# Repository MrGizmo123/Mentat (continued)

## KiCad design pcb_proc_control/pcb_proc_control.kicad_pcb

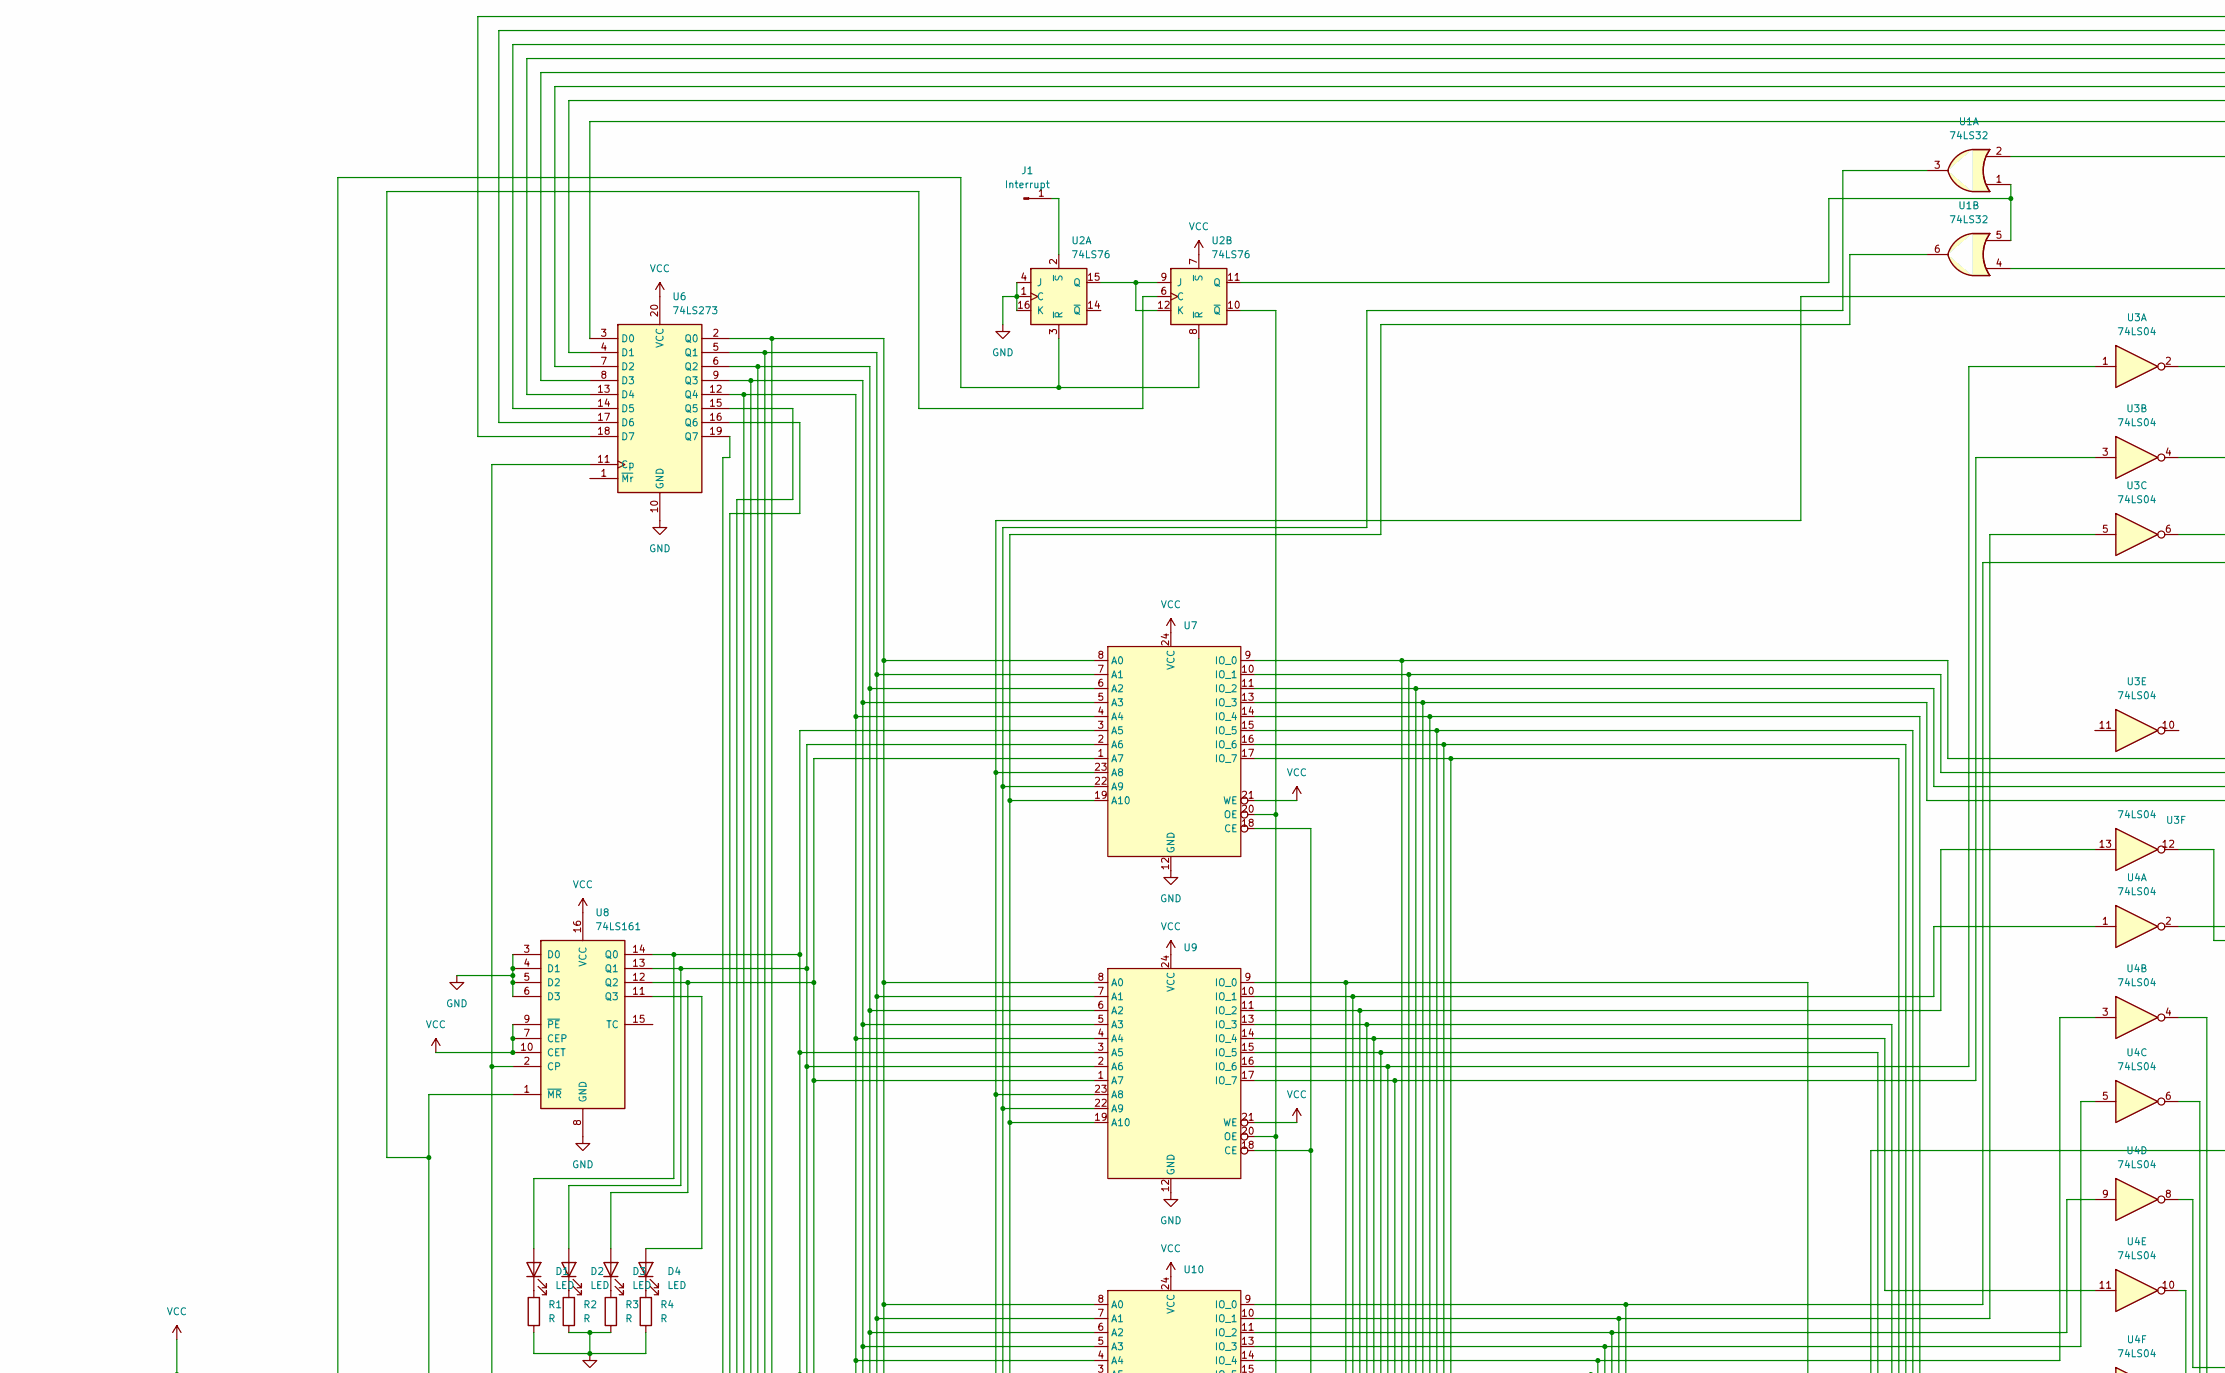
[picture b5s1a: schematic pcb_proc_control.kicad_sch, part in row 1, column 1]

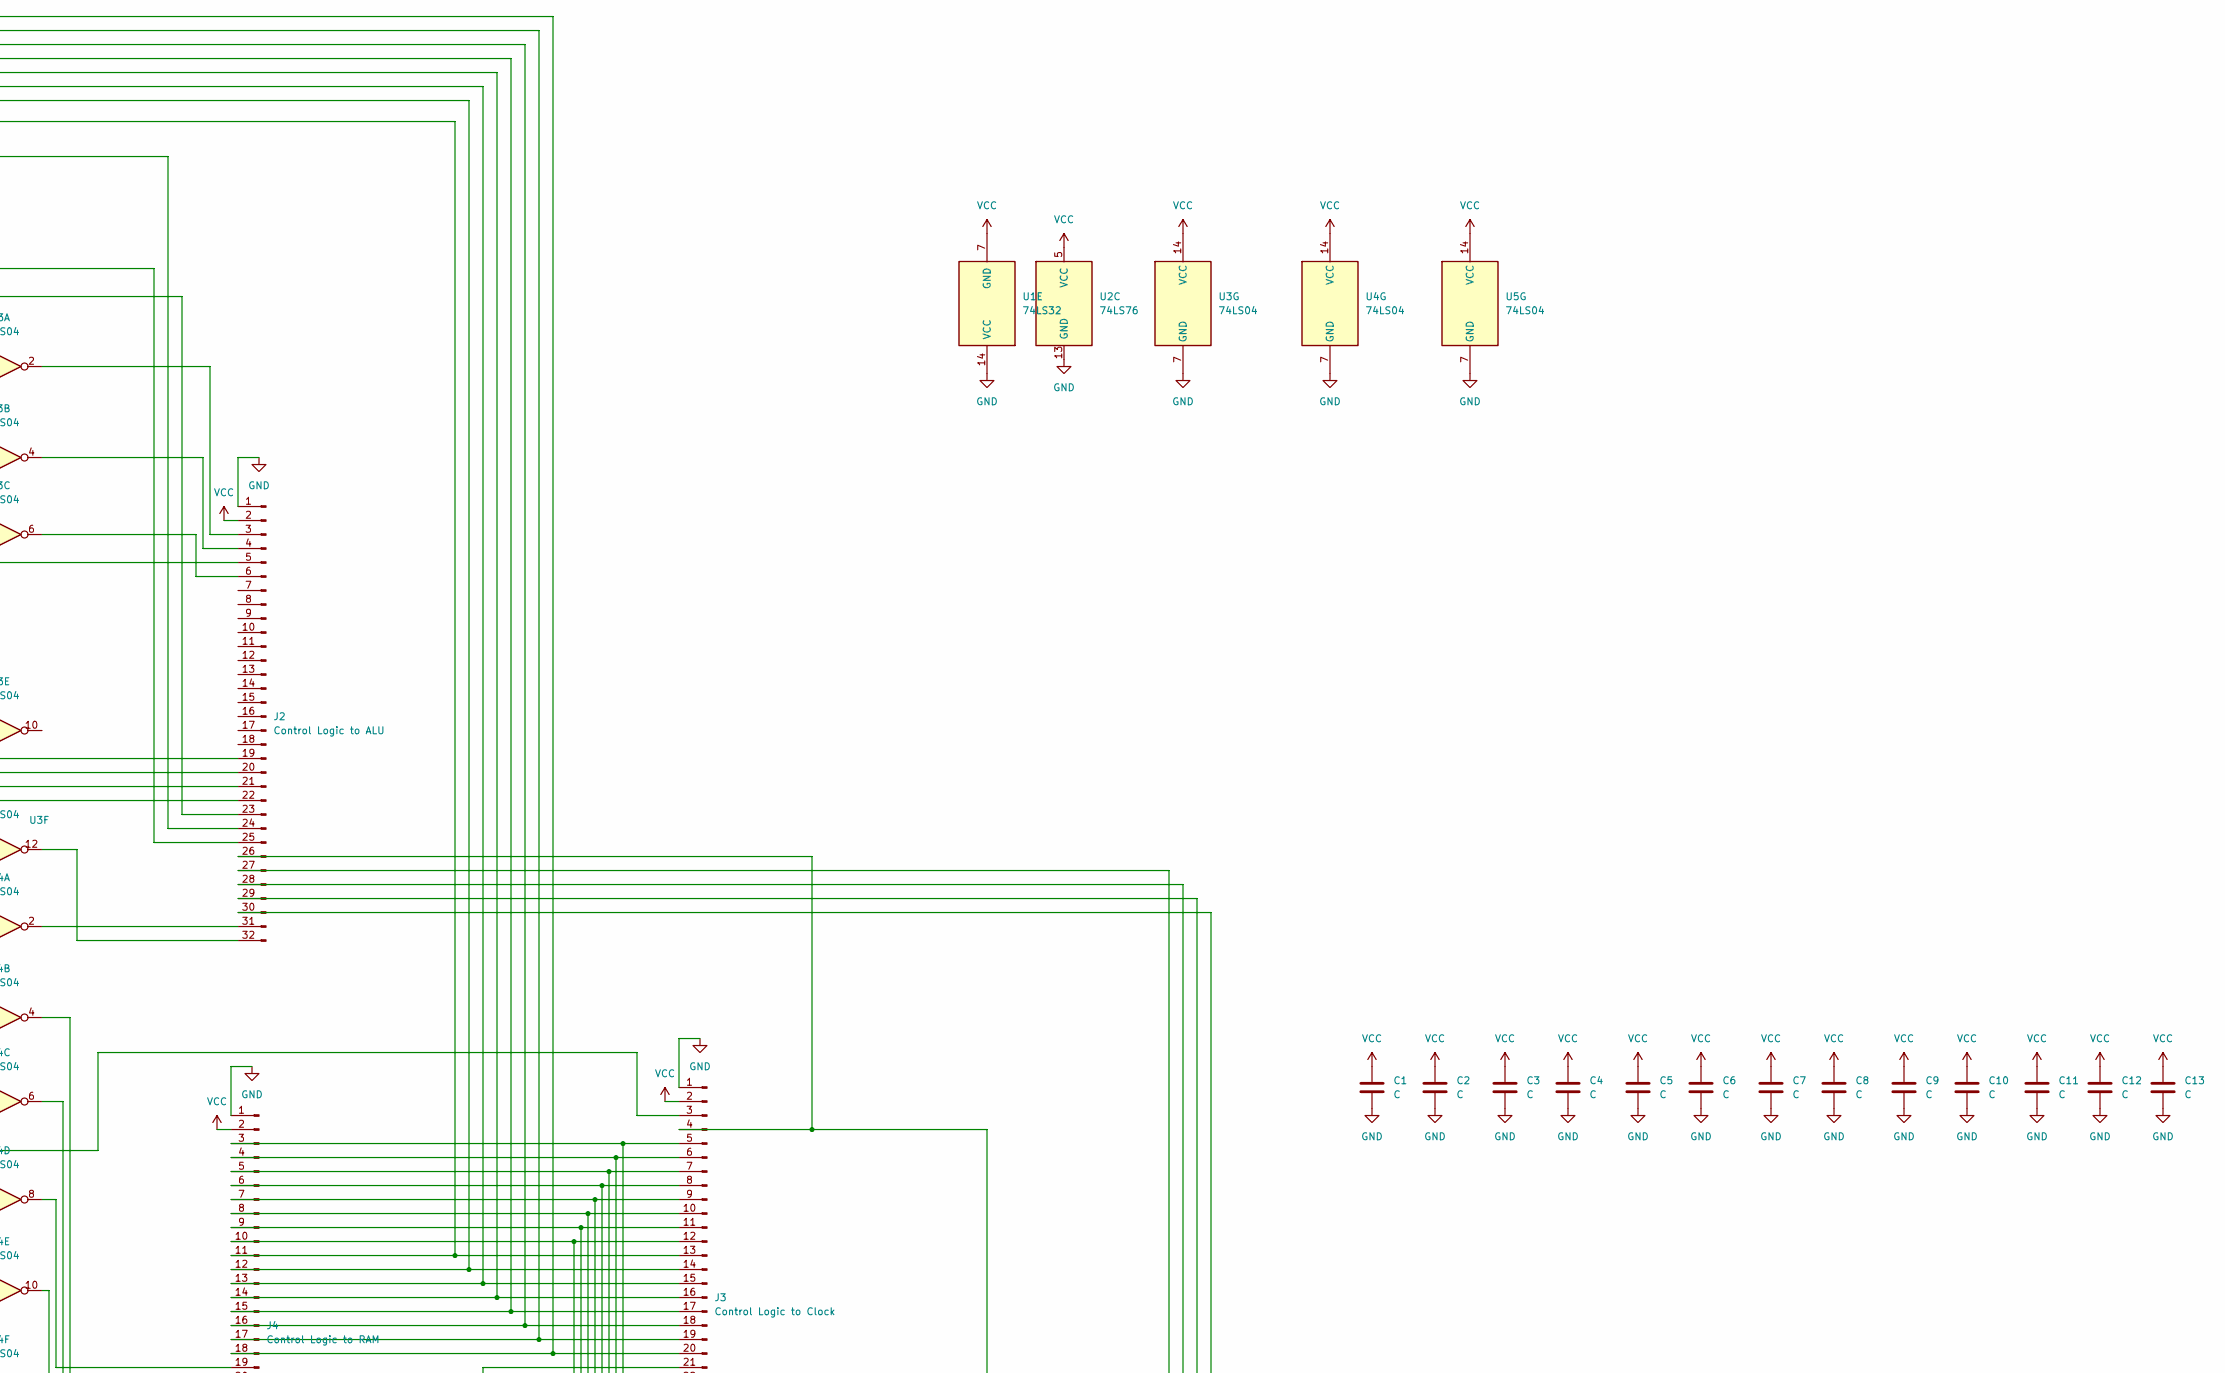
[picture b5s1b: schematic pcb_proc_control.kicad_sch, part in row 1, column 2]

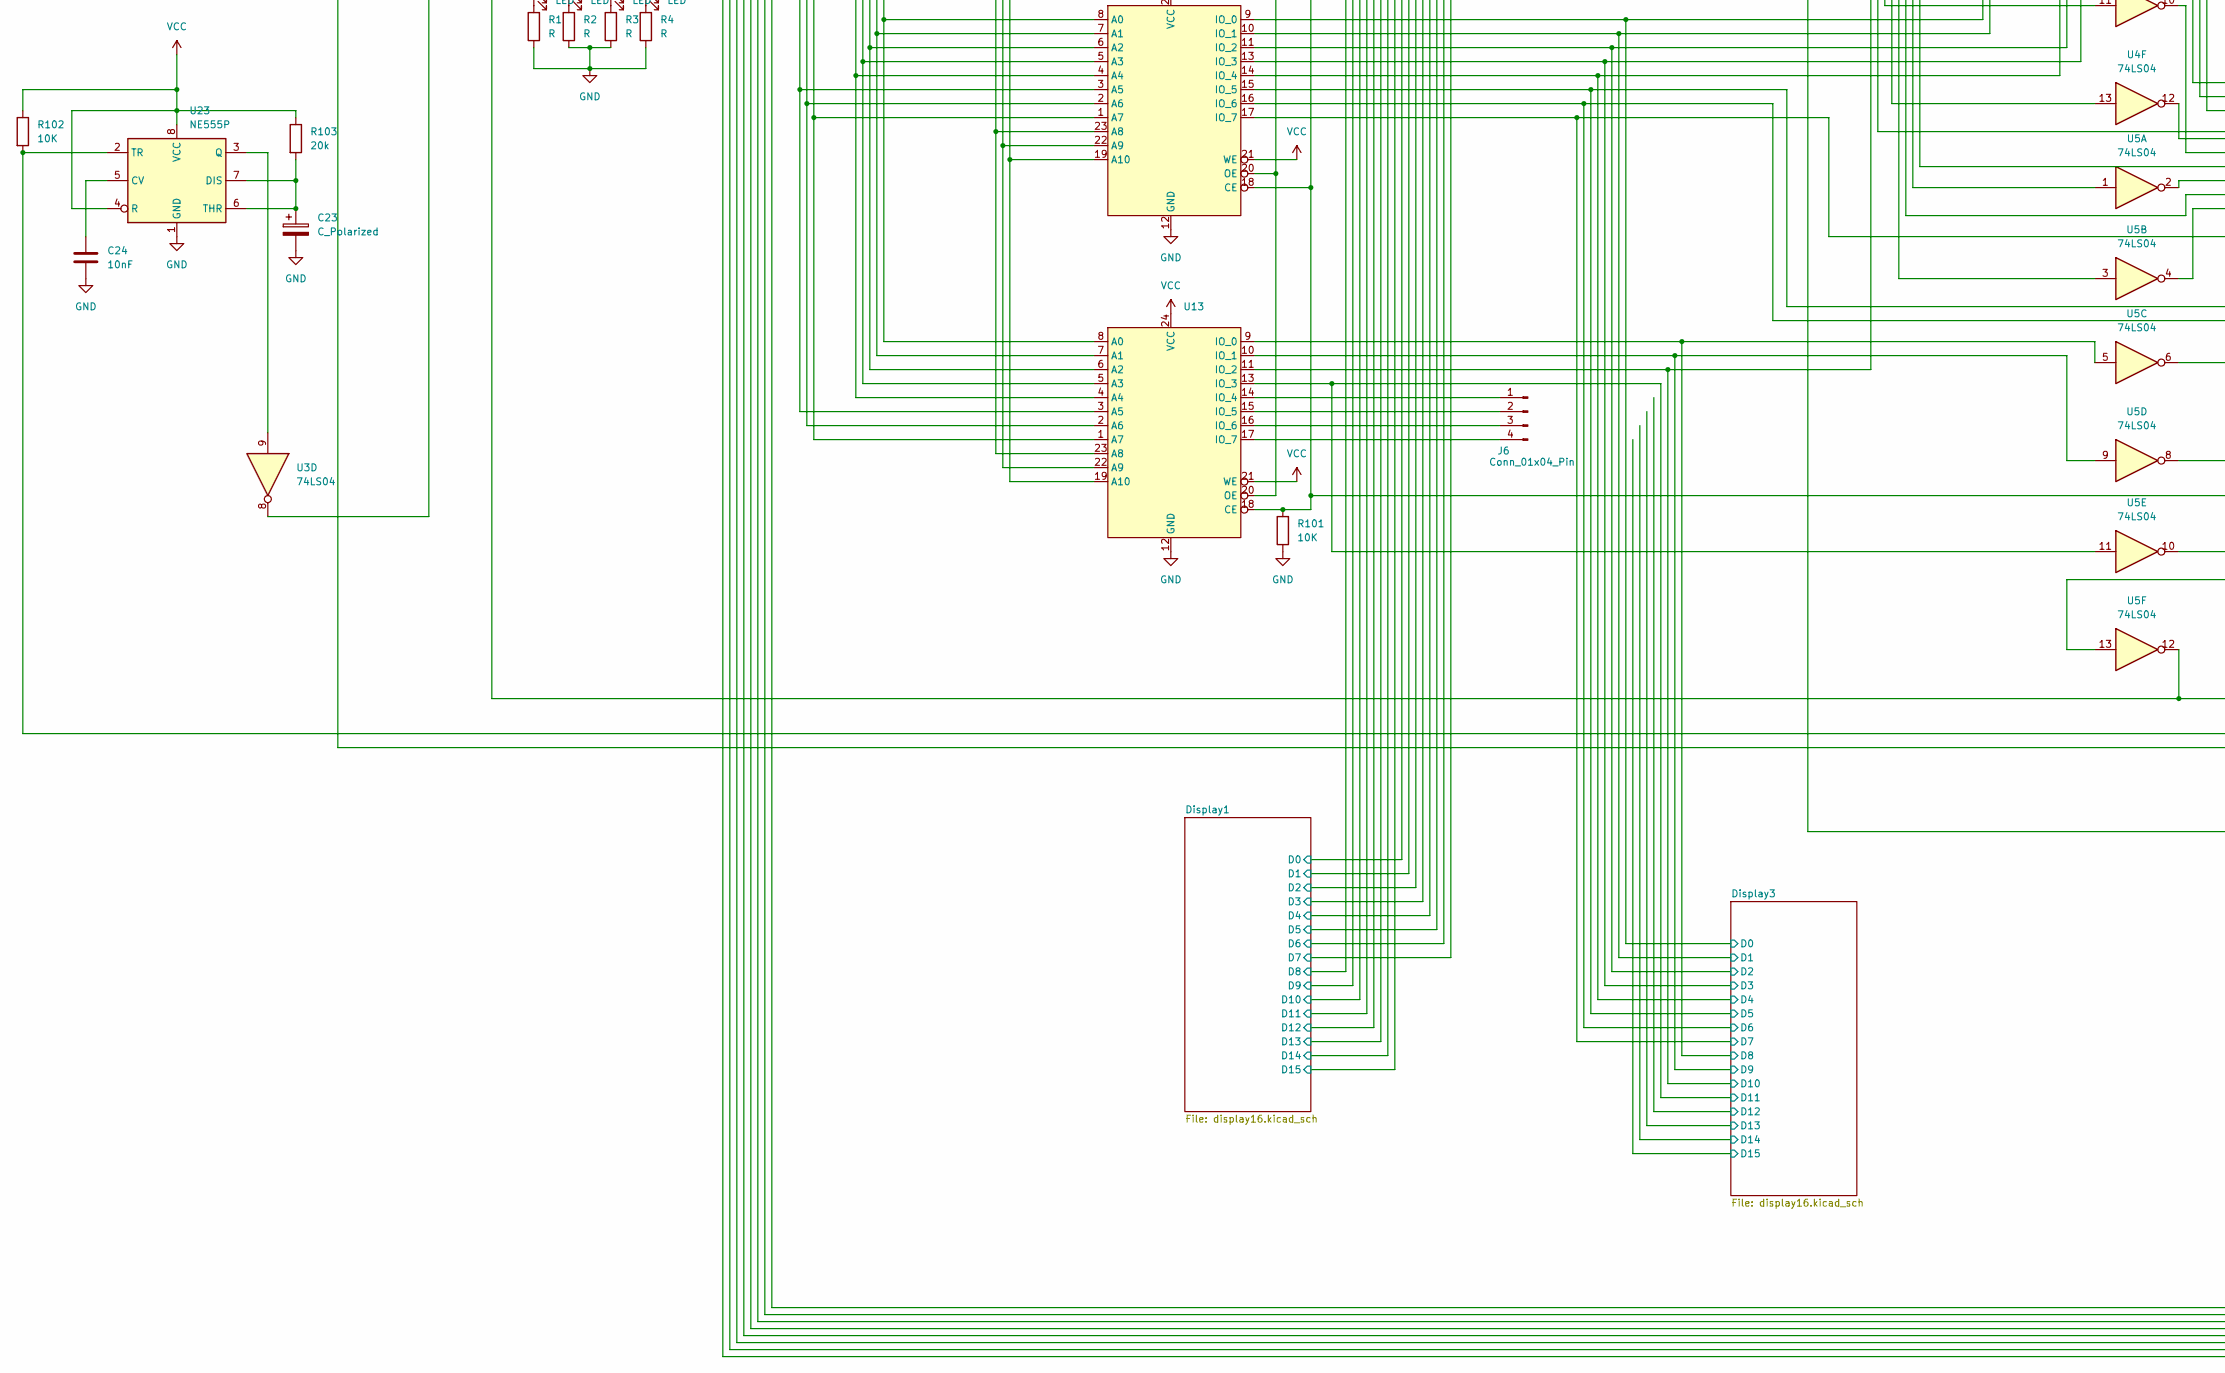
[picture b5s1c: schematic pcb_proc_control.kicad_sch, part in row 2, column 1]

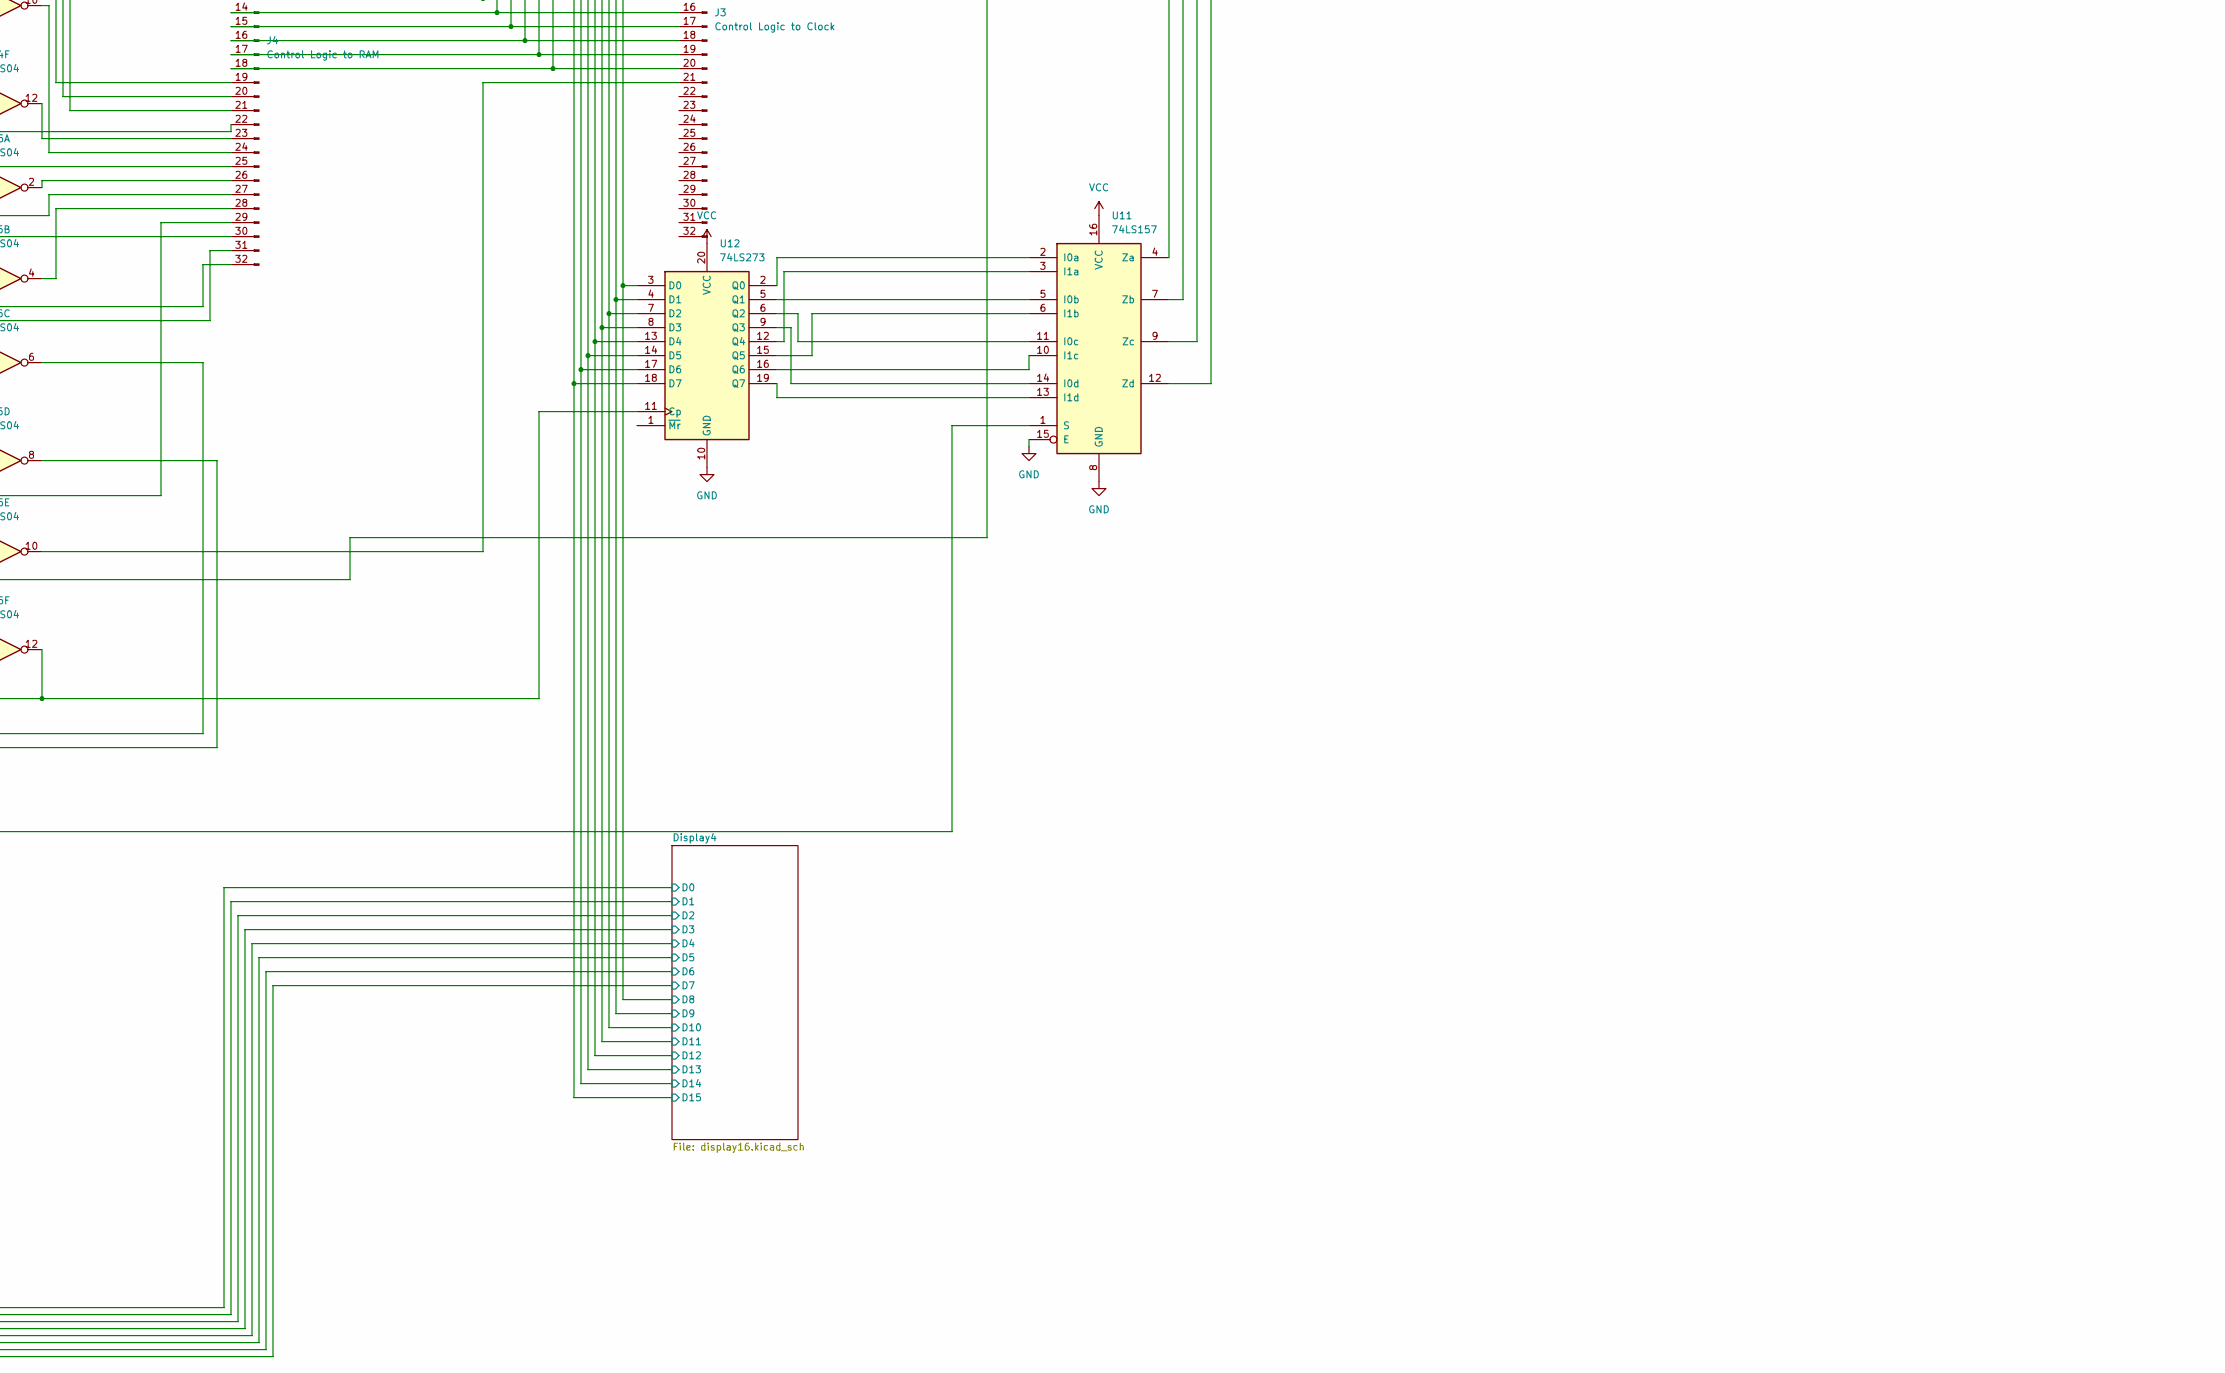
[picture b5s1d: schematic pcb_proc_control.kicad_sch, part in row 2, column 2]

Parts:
C1, C2, C3, C4, C5, C6, C7, C8, C9, C10, C11, C12, C13: C; C_0805_2012Metric
C23: C_Polarized; CP_Radial_D4.0mm_P1.50mm
C24: 10nF; C_Disc_D3.0mm_W1.6mm_P2.50mm
D1, D2, D3, D4: LED; LED_Rectangular_W5.0mm_H2.0mm
J1: Interrupt; PinHeader_1x01_P2.54mm_Vertical
J2: Control Logic to ALU; PinHeader_2x16_P2.54mm_Vertical
J3: Control Logic to Clock; PinHeader_2x16_P2.54mm_Vertical
J4: Control Logic to RAM; PinHeader_2x16_P2.54mm_Vertical
J6: Conn_01x04_Pin; PinHeader_1x04_P2.54mm_Vertical
R1, R2, R3, R4: R; R_0805_2012Metric
R101, R102: 10K; R_0805_2012Metric
R103: 20k; R_0805_2012Metric
U1: 74LS32; DIP-14_W7.62mm_Socket_LongPads
U2: 74LS76; DIP-16_W7.62mm_Socket_LongPads
U3, U4, U5: 74LS04; DIP-14_W7.62mm_Socket_LongPads
U6, U12: 74LS273; DIP-20_W7.62mm_Socket_LongPads
U7, U9, U10, U13: DIP-24_W15.24mm_Socket_LongPads
U8: 74LS161; DIP-16_W7.62mm_Socket_LongPads
U11: 74LS157; DIP-16_W7.62mm_Socket_LongPads
U23: NE555P; DIP-8_W7.62mm_Socket_LongPads

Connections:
/Display1/D0: J2.19, U7.9 (IO_0); also elsewhere on the board
/Display1/D1: J2.20, U7.10 (IO_1); also elsewhere on the board
/Display1/D2: J2.21, U7.11 (IO_2); also elsewhere on the board
/Display1/D3: J2.22, U7.13 (IO_3); also elsewhere on the board
/Display1/D4: J4.25, U7.14 (IO_4); also elsewhere on the board
/Display1/D5: U5.1, U7.15 (IO_5); also elsewhere on the board
/Display1/D6: J4.27, U7.16 (IO_6); also elsewhere on the board
/Display1/D7: U5.3, U7.17 (IO_7); also elsewhere on the board
/Display1/D8: U9.9 (IO_0), U11.1 (S); also elsewhere on the board
/Display1/D9: U4.1, U9.10 (IO_1); also elsewhere on the board
/Display1/D10: U3.13, U9.11 (IO_2); also elsewhere on the board
/Display1/D11: U4.13, U9.13 (IO_3); also elsewhere on the board
/Display1/D12: U4.11, U9.14 (IO_4); also elsewhere on the board
/Display1/D13: J4.22, U9.15 (IO_5); also elsewhere on the board
/Display1/D14: U3.1, U9.16 (IO_6); also elsewhere on the board
/Display1/D15: U3.3, U9.17 (IO_7); also elsewhere on the board
/Display3/D0: J2.5, U10.9 (IO_0); also elsewhere on the board
/Display3/D1: U3.5, U10.10 (IO_1); also elsewhere on the board
/Display3/D2: U4.9, U10.11 (IO_2); also elsewhere on the board
/Display3/D3: U4.5, U10.13 (IO_3); also elsewhere on the board
/Display3/D4: U4.3, U10.14 (IO_4); also elsewhere on the board
/Display3/D5: J4.32, U10.15 (IO_5); also elsewhere on the board
/Display3/D6: J4.31, U10.16 (IO_6); also elsewhere on the board
/Display3/D7: J4.30, U10.17 (IO_7); also elsewhere on the board
/Display3/D8: U5.5, U13.9 (IO_0); also elsewhere on the board
/Display3/D9: U5.9, U13.10 (IO_1); also elsewhere on the board
/Display3/D10: J3.3, U13.11 (IO_2); also elsewhere on the board
/Display3/D11: U5.11, U13.13 (IO_3); also elsewhere on the board
/Display4/D0: U6.2 (Q0), U7.8 (A0), U9.8 (A0), U10.8 (A0), U13.8 (A0); also elsewhere on the board
/Display4/D1: U6.5 (Q1), U7.7 (A1), U9.7 (A1), U10.7 (A1), U13.7 (A1); also elsewhere on the board
/Display4/D2: U6.6 (Q2), U7.6 (A2), U9.6 (A2), U10.6 (A2), U13.6 (A2); also elsewhere on the board
/Display4/D3: U6.9 (Q3), U7.5 (A3), U9.5 (A3), U10.5 (A3), U13.5 (A3); also elsewhere on the board
/Display4/D4: U6.12 (Q4), U7.4 (A4), U9.4 (A4), U10.4 (A4), U13.4 (A4); also elsewhere on the board
/Display4/D5: U6.15 (Q5); also elsewhere on the board
/Display4/D6: U6.16 (Q6); also elsewhere on the board
/Display4/D7: U6.19 (Q7); also elsewhere on the board
/Display4/D8: J3.5, J4.3, U12.3 (D0); also elsewhere on the board
/Display4/D9: J3.6, J4.4, U12.4 (D1); also elsewhere on the board
/Display4/D10: J3.7, J4.5, U12.7 (D2); also elsewhere on the board
/Display4/D11: J3.8, J4.6, U12.8 (D3); also elsewhere on the board
/Display4/D12: J3.9, J4.7, U12.13 (D4); also elsewhere on the board
/Display4/D13: J3.10, J4.8, U12.14 (D5); also elsewhere on the board
/Display4/D14: J3.11, J4.9, U12.17 (D6); also elsewhere on the board
/Display4/D15: J3.12, J4.10, U12.18 (D7); also elsewhere on the board
GND: C1.2, C2.2, C3.2, C4.2, C5.2, C6.2, C7.2, C8.2, C9.2, C10.2, C11.2, C12.2, C13.2, C23.2, C24.2, J2.1, J3.1, J4.1, R1.1, R2.1, R3.1, R4.1, R101.1, U1.14 (VCC), U2.1 (C), U2.4 (J), U2.13 (GND), U2.16 (K), U3.7 (GND), U4.7 (GND), U5.7 (GND), U6.10 (GND), U7.12 (GND), U8.3 (D0), U8.4 (D1), U8.5 (D2), U8.6 (D3), U8.8 (GND), U9.12 (GND), U10.12 (GND), U11.8 (GND), U11.15 (E), U12.10 (GND), U13.12 (GND), U23.1 (GND); also elsewhere on the board
unnamed: D1.2 (A), U7.3 (A5), U8.14 (Q0), U9.3 (A5), U10.3 (A5), U13.3 (A5)
unnamed: D1.1 (K), R1.2
unnamed: D2.2 (A), U7.2 (A6), U8.13 (Q1), U9.2 (A6), U10.2 (A6), U13.2 (A6)
unnamed: D2.1 (K), R2.2
unnamed: D3.2 (A), U7.1 (A7), U8.12 (Q2), U9.1 (A7), U10.1 (A7), U13.1 (A7)
unnamed: D3.1 (K), R3.2
unnamed: D4.2 (A), U8.11 (Q3)
unnamed: D4.1 (K), R4.2
unnamed: J1.1, U2.2 (~S)
unnamed: J2.3, U3.2
unnamed: J2.4, U3.4
unnamed: J2.6, U3.6
unnamed: J2.23, U7.23 (A8), U9.23 (A8), U10.23 (A8), U13.23 (A8)
unnamed: J2.24, U1.2
unnamed: J2.25, U1.4
unnamed: J2.26, J3.4, U5.13
unnamed: J2.27, U11.4 (Za)
unnamed: J2.28, U11.7 (Zb)
unnamed: J2.29, U11.9 (Zc)
unnamed: J2.30, U11.12 (Zd)
unnamed: J2.31, U4.2
unnamed: J2.32, U3.12
unnamed: J3.13, J4.11, U6.3 (D0)
unnamed: J3.14, J4.12, U6.4 (D1)
unnamed: J3.15, J4.13, U6.7 (D2)
unnamed: J3.16, J4.14, U6.8 (D3)
unnamed: J3.17, J4.15, U6.13 (D4)
unnamed: J3.18, J4.16, U6.14 (D5)
unnamed: J3.19, J4.17, U6.17 (D6)
unnamed: J3.20, J4.18, U6.18 (D7)
unnamed: J3.21, U5.10
unnamed: J4.19, U4.8
unnamed: J4.20, U4.6
unnamed: J4.21, U4.4
unnamed: J4.23, U4.12
unnamed: J4.24, U4.10
unnamed: J4.26, U5.2
unnamed: J4.28, U5.4
unnamed: J4.29, R101.2, U7.18 (CE), U9.18 (CE), U10.18 (CE), U13.18 (CE)
unnamed: J6.1, U13.14 (IO_4)
unnamed: J6.2, U13.15 (IO_5)
unnamed: J6.3, U13.16 (IO_6)
unnamed: J6.4, U13.17 (IO_7)
unnamed: U2.9 (J), U2.12 (K), U2.15 (Q)
unnamed: U2.3 (~R), U2.8 (~R), U5.8
unnamed: U2.6 (C), U3.8, U8.1 (~MR)
unnamed: U1.1, U1.5, U2.11 (Q)
unnamed: U1.3, U7.22 (A9), U9.22 (A9), U10.22 (A9), U13.22 (A9)
unnamed: U1.6, U7.19 (A10), U9.19 (A10), U10.19 (A10), U13.19 (A10)
unnamed: U2.10 (~Q), U7.20 (OE), U9.20 (OE), U10.20 (OE), U13.20 (OE)
unnamed: U11.2 (I0a), U12.2 (Q0)
unnamed: U11.5 (I0b), U12.5 (Q1)
unnamed: U11.11 (I0c), U12.6 (Q2)
unnamed: U11.14 (I0d), U12.9 (Q3)
unnamed: U11.3 (I1a), U12.12 (Q4)
unnamed: U11.6 (I1b), U12.15 (Q5)
unnamed: U11.10 (I1c), U12.16 (Q6)
unnamed: U11.13 (I1d), U12.19 (Q7)
unnamed: U5.12, U6.11 (Cp), U8.2 (CP), U12.11 (Cp)
unnamed: C24.1, U23.5 (CV)
unnamed: C23.1, R103.2, U23.6 (THR), U23.7 (DIS)
unnamed: U3.9, U23.3 (Q)
unnamed: R102.2, U5.6, U23.2 (TR)
VCC: C1.1, C2.1, C3.1, C4.1, C5.1, C6.1, C7.1, C8.1, C9.1, C10.1, C11.1, C12.1, C13.1, J2.2, J3.2, J4.2, R102.1, R103.1, U1.7 (GND), U2.5 (VCC), U2.7 (~S), U3.14 (VCC), U4.14 (VCC), U5.14 (VCC), U6.20 (VCC), U7.21 (WE), U7.24 (VCC), U8.7 (CEP), U8.9 (~PE), U8.10 (CET), U8.16 (VCC), U9.21 (WE), U9.24 (VCC), U10.21 (WE), U10.24 (VCC), U11.16 (VCC), U12.20 (VCC), U13.21 (WE), U13.24 (VCC), U23.4 (R), U23.8 (VCC); also elsewhere on the board
